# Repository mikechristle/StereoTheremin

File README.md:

# StereoTheremin
II'm sure you are familiar with the Theremin. 
It is a musical instrument that uses hand movements to control pitch and volume. 
One hand controls pitch, and the other hand control volume. 
I like the expressiveness of a no contact instrument,
 but controlling two variables is just too limiting. 
 With my version each hand controls both pitch and volume. 
 The up/down motion controls volume, and the right/left motion controls pitch. 
 This way the right hand plays treble and the left hand plays base, like a piano.
## Code
The micropython code that runs on the Raspberry PI Pico.
## Control
The python code that runs on a PC or a tablet to control the Stereo Theremin.
## PCB
The KiCad files for the printed circuit board. 
Version 10.0.

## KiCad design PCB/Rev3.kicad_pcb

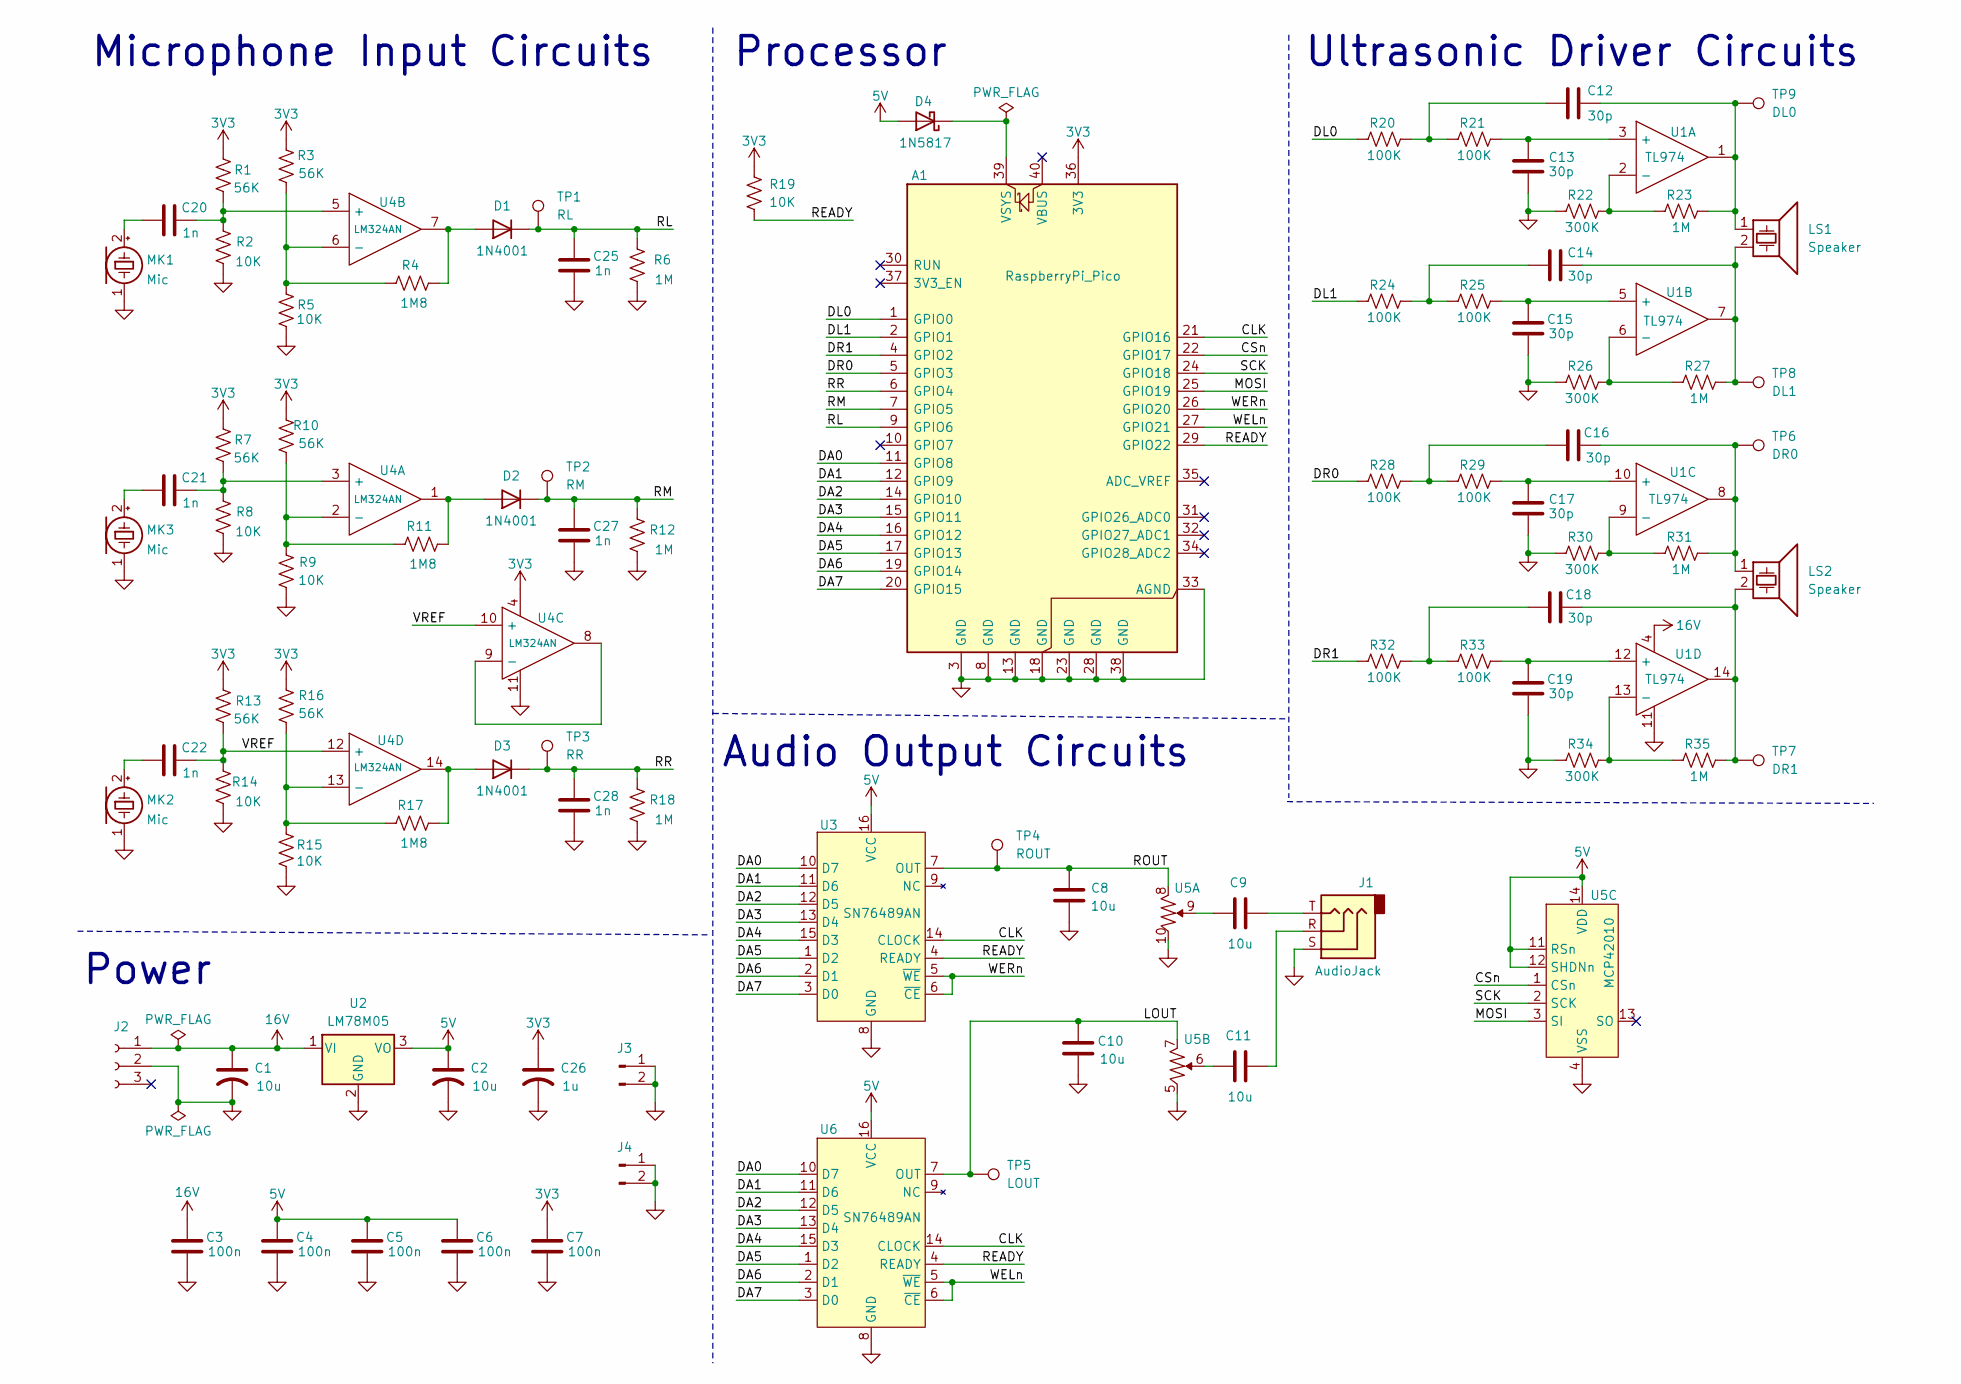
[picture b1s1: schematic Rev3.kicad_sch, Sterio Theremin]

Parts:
A1: RaspberryPi_Pico; RaspberryPi_Pico_Common_THT
C1, C2: 10u; CP_Radial_D6.3mm_P2.50mm
C3, C4, C5, C6, C7: 100n; C_Disc_D3.0mm_W1.6mm_P2.50mm
C8, C9, C10, C11: 10u; C_Disc_D4.3mm_W1.9mm_P5.00mm
C12, C13, C14, C15, C16, C17, C18, C19: 30p; C_Disc_D4.3mm_W1.9mm_P5.00mm
C20, C21, C22, C25, C27, C28: 1n; C_Disc_D4.3mm_W1.9mm_P5.00mm
C26: 1u; CP_Radial_D5.0mm_P2.50mm
D1, D2, D3: 1N4001; D_A-405_P7.62mm_Horizontal
D4: 1N5817; D_A-405_P7.62mm_Horizontal
J1: AudioJack; STX-3000
J2: Conn_01x03_Socket; BarrelJack_Kycon_KLDX-0202-xC_Horizontal
J3, J4: Conn_01x02_Pin; PinHeader_1x02_P2.54mm_Vertical
LS1, LS2: Speaker; Ultra Sonic TR
MK1, MK2, MK3: Mic; Ultra Sonic TR
R1, R3, R7, R10, R13, R16: 56K; R_Axial_DIN0204_L3.6mm_D1.6mm_P5.08mm_Horizontal
R2, R5, R8, R9, R14, R15, R19: 10K; R_Axial_DIN0204_L3.6mm_D1.6mm_P5.08mm_Horizontal
R4, R11, R17: 1M8; R_Axial_DIN0204_L3.6mm_D1.6mm_P5.08mm_Horizontal
R6, R12, R18, R23, R27, R31, R35: 1M; R_Axial_DIN0204_L3.6mm_D1.6mm_P5.08mm_Horizontal
R20, R21, R24, R25, R28, R29, R32, R33: 100K; R_Axial_DIN0204_L3.6mm_D1.6mm_P5.08mm_Horizontal
R22, R26, R30, R34: 300K; R_Axial_DIN0204_L3.6mm_D1.6mm_P5.08mm_Horizontal
TP1: RL; TestPoint_Loop_D2.50mm_Drill1.85mm
TP2: RM; TestPoint_Loop_D2.50mm_Drill1.85mm
TP3: RR; TestPoint_Loop_D2.50mm_Drill1.85mm
TP4: ROUT; TestPoint_Loop_D2.50mm_Drill1.85mm
TP5: LOUT; TestPoint_Loop_D2.50mm_Drill1.85mm
TP6: DR0; TestPoint_Loop_D2.50mm_Drill1.85mm
TP7: DR1; TestPoint_Loop_D2.50mm_Drill1.85mm
TP8: DL1; TestPoint_Loop_D2.50mm_Drill1.85mm
TP9: DL0; TestPoint_Loop_D2.50mm_Drill1.85mm
U1: TL974; DIP-14_W7.62mm
U2: LM78M05; TO-252-2
U3, U6: SN76489AN; DIP-16_W7.62mm
U4: LM324AN; DIP-14_W7.62mm
U5: MCP42010; DIP-14_W7.62mm

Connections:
3V3: A1.36 (3V3), C7.1, C26.1, R1.2, R3.2, R7.2, R10.2, R13.2, R16.2, R19.1, U4.4
5V: C2.1, C4.1, C5.1, C6.1, D4.2 (A), U2.3 (VO), U3.16 (VCC), U5.11 (RSn), U5.12 (SHDNn), U5.14 (VDD), U6.16 (VCC)
16V: C1.1, C3.1, J2.1, U1.4, U2.1 (VI)
/CLK: A1.21 (GPIO16), U3.14 (CLOCK), U6.14 (CLOCK)
/CSn: A1.22 (GPIO17), U5.1 (CSn)
/DA0: A1.11 (GPIO8), U3.10 (D7), U6.10 (D7)
/DA1: A1.12 (GPIO9), U3.11 (D6), U6.11 (D6)
/DA2: A1.14 (GPIO10), U3.12 (D5), U6.12 (D5)
/DA3: A1.15 (GPIO11), U3.13 (D4), U6.13 (D4)
/DA4: A1.16 (GPIO12), U3.15 (D3), U6.15 (D3)
/DA5: A1.17 (GPIO13), U3.1 (D2), U6.1 (D2)
/DA6: A1.19 (GPIO14), U3.2 (D1), U6.2 (D1)
/DA7: A1.20 (GPIO15), U3.3 (D0), U6.3 (D0)
/DL0: A1.1 (GPIO0), R20.1
/DL1: A1.2 (GPIO1), R24.1
/DR0: A1.5 (GPIO3), R28.1
/DR1: A1.4 (GPIO2), R32.1
/LOUT: C10.2, TP5.1 (1_1), U5.7, U6.7 (OUT)
/MOSI: A1.25 (GPIO19), U5.3 (SI)
/READY: A1.29 (GPIO22), R19.2, U3.4 (READY), U6.4 (READY)
/RL: A1.9 (GPIO6), C25.1, D1.1 (K), R6.2, TP1.1 (1_1)
/RM: A1.7 (GPIO5), C27.1, D2.1 (K), R12.2, TP2.1 (1_1)
/ROUT: C8.2, TP4.1 (1_1), U3.7 (OUT), U5.8
/RR: A1.6 (GPIO4), C28.1, D3.1 (K), R18.2, TP3.1 (1_1)
/SCK: A1.24 (GPIO18), U5.2 (SCK)
/VREF: C22.2, R13.1, R14.2, U4.10 (+), U4.12 (+)
/WELn: A1.27 (GPIO21), U6.5 (~WE), U6.6 (~CE)
/WERn: A1.26 (GPIO20), U3.5 (~WE), U3.6 (~CE)
GND: A1.3 (GND), A1.8 (GND), A1.13 (GND), A1.18 (GND), A1.23 (GND), A1.28 (GND), A1.33 (AGND), A1.38 (GND), C1.2, C2.2, C3.2, C4.2, C5.2, C6.2, C7.2, C8.1, C10.1, C13.2, C15.2, C17.2, C19.2, C25.2, C26.2, C27.2, C28.2, J1.S, J2.2, J3.1, J3.2, J4.1, J4.2, MK1.1 (-), MK2.1 (-), MK3.1 (-), R2.1, R5.2, R6.1, R8.1, R9.2, R12.1, R14.1, R15.2, R18.1, R22.1, R26.1, R30.1, R34.1, U1.11, U2.2 (GND), U3.8 (GND), U4.11, U5.4 (VSS), U5.5, U5.10, U6.8 (GND)
unnamed: A1.39 (VSYS), D4.1 (K)
unnamed: C9.1, J1.T
unnamed: C9.2, U5.9
unnamed: C11.1, J1.R
unnamed: C11.2, U5.6
unnamed: C12.1, R20.2, R21.1
unnamed: C12.2, LS1.1, R23.2, TP9.1 (1_1), U1.1
unnamed: C14.1, R24.2, R25.1
unnamed: C14.2, LS1.2, R27.2, TP8.1 (1_1), U1.7
unnamed: C16.1, R28.2, R29.1
unnamed: C16.2, LS2.1, R31.2, TP6.1 (1_1), U1.8
unnamed: C18.1, R32.2, R33.1
unnamed: C18.2, LS2.2, R35.2, TP7.1 (1_1), U1.14
unnamed: D1.2 (A), R4.2, U4.7
unnamed: D2.2 (A), R11.2, U4.1
unnamed: D3.2 (A), R17.2, U4.14
unnamed: C20.1, MK1.2 (+)
unnamed: C22.1, MK2.2 (+)
unnamed: C21.1, MK3.2 (+)
unnamed: C13.1, R21.2, U1.3 (+)
unnamed: R22.2, R23.1, U1.2 (-)
unnamed: C15.1, R25.2, U1.5 (+)
unnamed: R26.2, R27.1, U1.6 (-)
unnamed: C17.1, R29.2, U1.10 (+)
unnamed: R30.2, R31.1, U1.9 (-)
unnamed: C19.1, R33.2, U1.12 (+)
unnamed: R34.2, R35.1, U1.13 (-)
unnamed: C21.2, R7.1, R8.2, U4.3 (+)
unnamed: R9.1, R10.1, R11.1, U4.2 (-)
unnamed: C20.2, R1.1, R2.2, U4.5 (+)
unnamed: R3.1, R4.1, R5.1, U4.6 (-)
unnamed: U4.8, U4.9 (-)
unnamed: R15.1, R16.1, R17.1, U4.13 (-)

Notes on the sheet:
Audio Output Circuits
Processor
Power
Microphone Input Circuits
Ultrasonic Driver Circuits

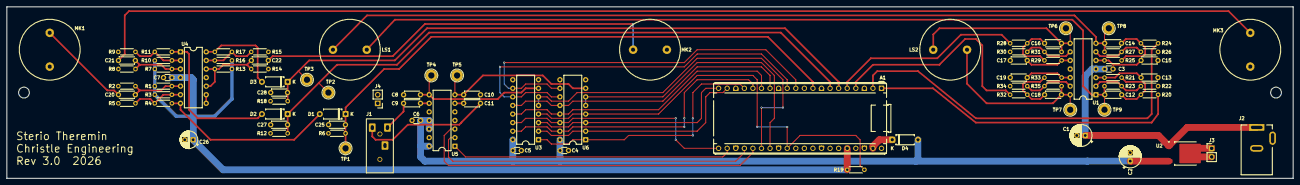
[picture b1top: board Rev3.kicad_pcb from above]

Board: 2 copper layers, 381.0 x 50.8 mm, 90 parts (0 on the bottom side), 62 nets.

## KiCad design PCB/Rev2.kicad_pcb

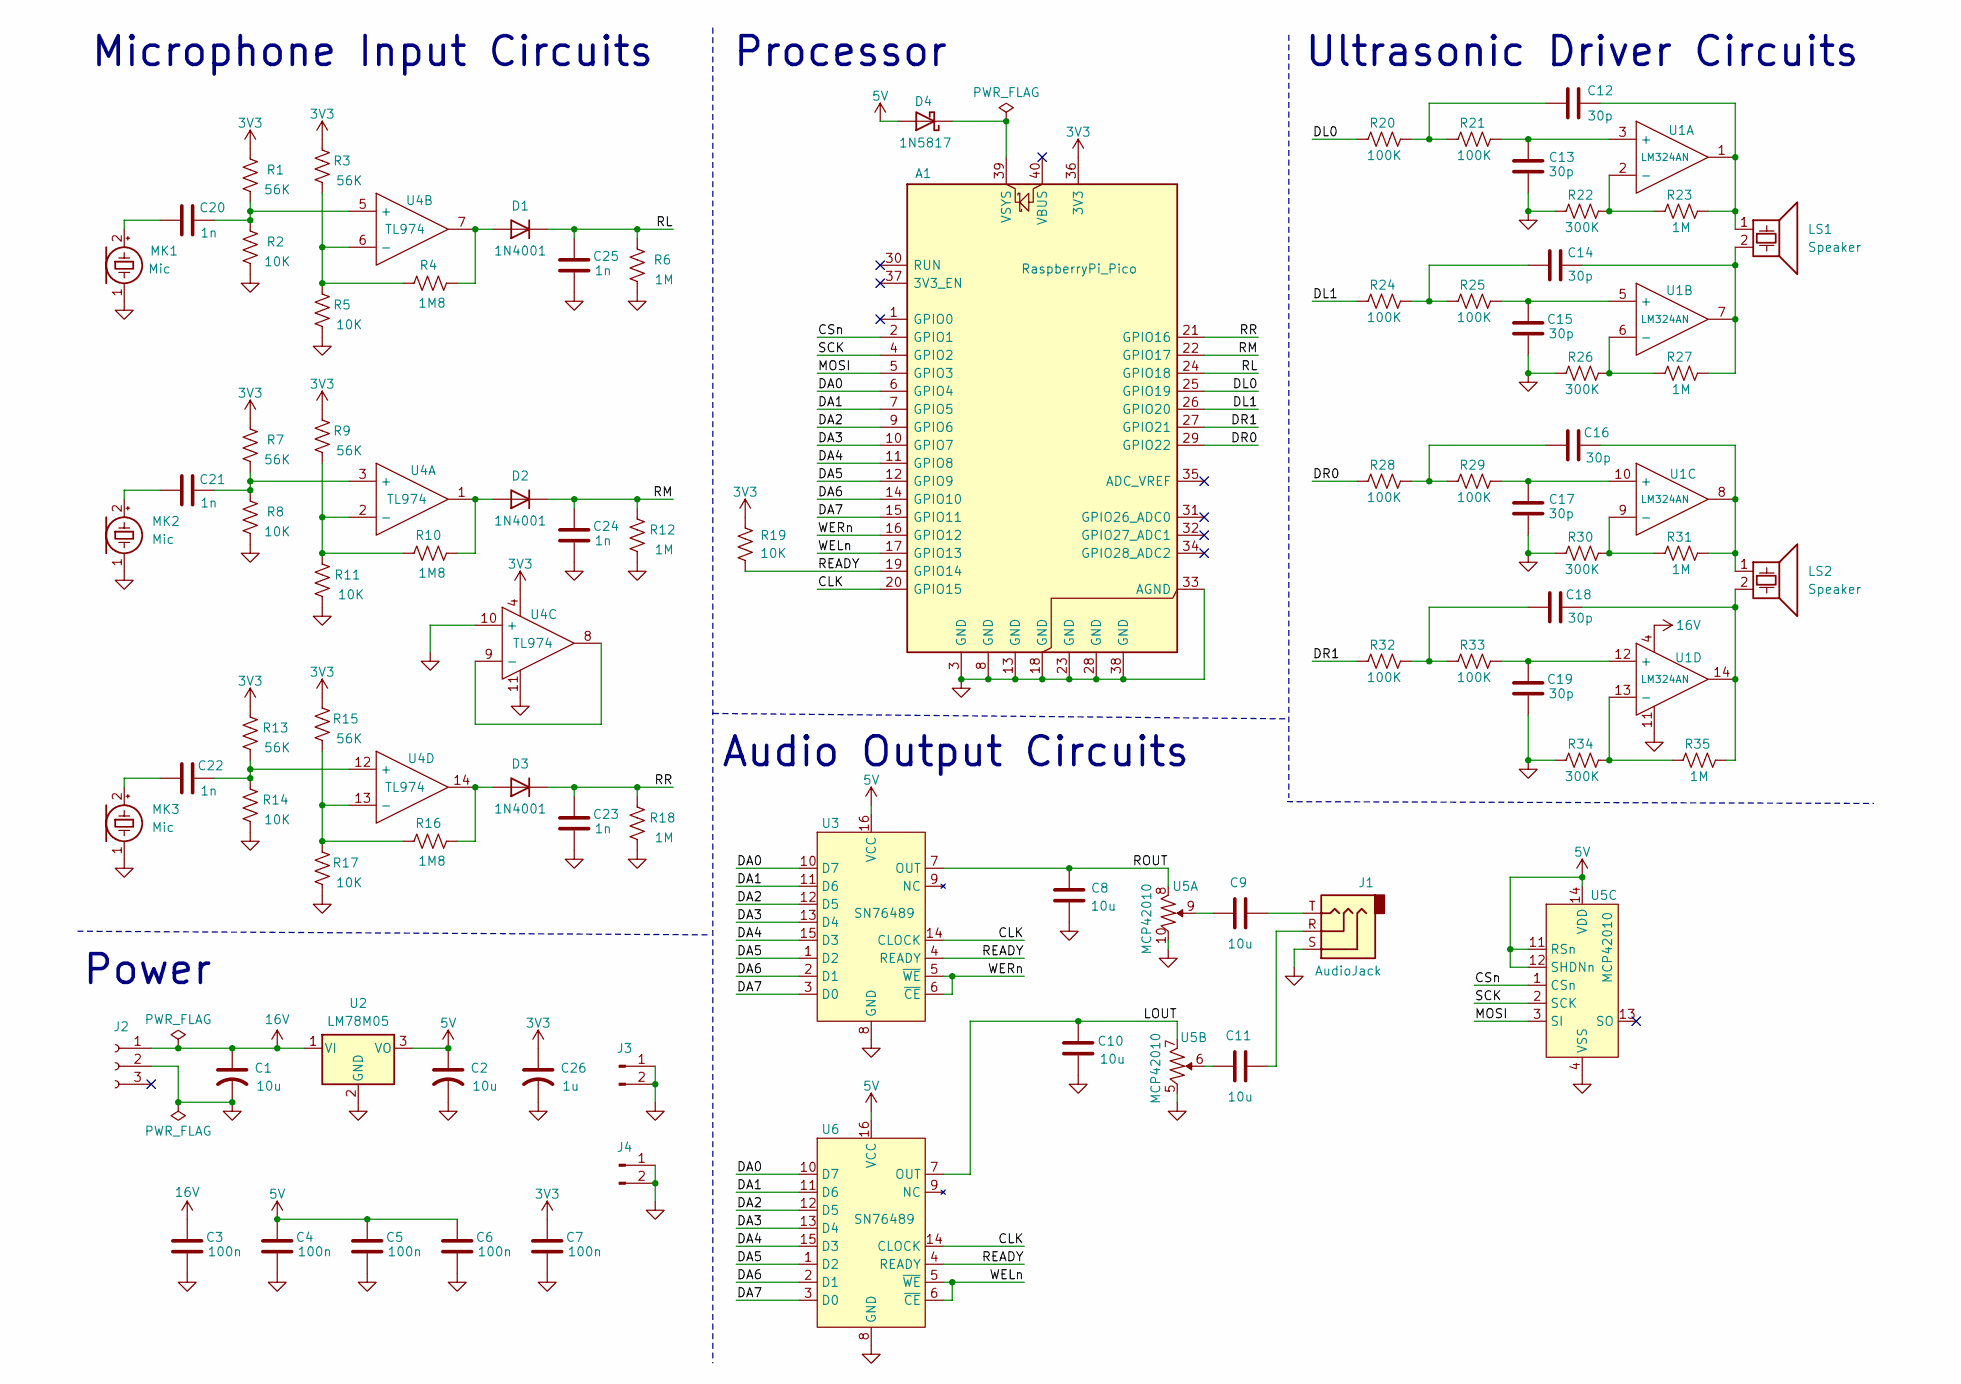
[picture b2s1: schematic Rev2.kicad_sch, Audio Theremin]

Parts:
A1: RaspberryPi_Pico; RaspberryPi_Pico_Common_THT
C1, C2: 10u; CP_Radial_D6.3mm_P2.50mm
C3, C4, C5, C6, C7: 100n; C_Disc_D3.0mm_W1.6mm_P2.50mm
C8, C9, C10, C11: 10u; C_Disc_D4.3mm_W1.9mm_P5.00mm
C12, C13, C14, C15, C16, C17, C18, C19: 30p; C_Disc_D4.3mm_W1.9mm_P5.00mm
C20, C21, C22, C23, C24, C25: 1n; C_Disc_D4.3mm_W1.9mm_P5.00mm
C26: 1u; CP_Radial_D5.0mm_P2.50mm
D1, D2, D3: 1N4001; D_DO-41_SOD81_P10.16mm_Horizontal
D4: 1N5817; D_DO-41_SOD81_P10.16mm_Horizontal
J1: AudioJack; STX-3000
J2: Conn_01x03_Socket; BarrelJack_Kycon_KLDX-0202-xC_Horizontal
J3, J4: Conn_01x02_Pin; PinHeader_1x02_P2.54mm_Vertical
LS1, LS2: Speaker; PinHeader_1x02_P2.54mm_Vertical
MK1, MK2, MK3: Mic; PinHeader_1x02_P2.54mm_Vertical
R1, R3, R7, R9, R13, R15: 56K; R_Axial_DIN0204_L3.6mm_D1.6mm_P5.08mm_Horizontal
R2, R5, R8, R11, R14, R17, R19: 10K; R_Axial_DIN0204_L3.6mm_D1.6mm_P5.08mm_Horizontal
R4, R10, R16: 1M8; R_Axial_DIN0204_L3.6mm_D1.6mm_P5.08mm_Horizontal
R6, R12, R18, R23, R27, R31, R35: 1M; R_Axial_DIN0204_L3.6mm_D1.6mm_P5.08mm_Horizontal
R20, R21, R24, R25, R28, R29, R32, R33: 100K; R_Axial_DIN0204_L3.6mm_D1.6mm_P5.08mm_Horizontal
R22, R26, R30, R34: 300K; R_Axial_DIN0204_L3.6mm_D1.6mm_P5.08mm_Horizontal
U1: LM324AN; DIP-14_W7.62mm
U2: LM78M05; TO-252-2
U3, U6: SN76489; DIP-16_W7.62mm
U4: TL974; DIP-14_W7.62mm
U5: MCP42010; DIP-14_W7.62mm

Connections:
3V3: A1.36 (3V3), C7.1, C26.1, R1.2, R3.2, R7.2, R9.2, R13.2, R15.2, R19.1, U4.4
5V: C2.1, C4.1, C5.1, C6.1, D4.2 (A), U2.3 (VO), U3.16 (VCC), U5.11 (RSn), U5.12 (SHDNn), U5.14 (VDD), U6.16 (VCC)
16V: C1.1, C3.1, J2.1, U1.4, U2.1 (VI)
/CLK: A1.20 (GPIO15), U3.14 (CLOCK), U6.14 (CLOCK)
/CSn: A1.2 (GPIO1), U5.1 (CSn)
/DA0: A1.6 (GPIO4), U3.10 (D7), U6.10 (D7)
/DA1: A1.7 (GPIO5), U3.11 (D6), U6.11 (D6)
/DA2: A1.9 (GPIO6), U3.12 (D5), U6.12 (D5)
/DA3: A1.10 (GPIO7), U3.13 (D4), U6.13 (D4)
/DA4: A1.11 (GPIO8), U3.15 (D3), U6.15 (D3)
/DA5: A1.12 (GPIO9), U3.1 (D2), U6.1 (D2)
/DA6: A1.14 (GPIO10), U3.2 (D1), U6.2 (D1)
/DA7: A1.15 (GPIO11), U3.3 (D0), U6.3 (D0)
/DL0: A1.25 (GPIO19), R20.1
/DL1: A1.26 (GPIO20), R24.1
/DR0: A1.29 (GPIO22), R28.1
/DR1: A1.27 (GPIO21), R32.1
/LOUT: C10.2, U5.7, U6.7 (OUT)
/MOSI: A1.5 (GPIO3), U5.3 (SI)
/READY: A1.19 (GPIO14), R19.2, U3.4 (READY), U6.4 (READY)
/RL: A1.24 (GPIO18), C25.1, D1.1 (K), R6.2
/RM: A1.22 (GPIO17), C24.1, D2.1 (K), R12.2
/ROUT: C8.2, U3.7 (OUT), U5.8
/RR: A1.21 (GPIO16), C23.1, D3.1 (K), R18.2
/SCK: A1.4 (GPIO2), U5.2 (SCK)
/WELn: A1.17 (GPIO13), U6.5 (~WE), U6.6 (~CE)
/WERn: A1.16 (GPIO12), U3.5 (~WE), U3.6 (~CE)
GND: A1.3 (GND), A1.8 (GND), A1.13 (GND), A1.18 (GND), A1.23 (GND), A1.28 (GND), A1.33 (AGND), A1.38 (GND), C1.2, C2.2, C3.2, C4.2, C5.2, C6.2, C7.2, C8.1, C10.1, C13.2, C15.2, C17.2, C19.2, C23.2, C24.2, C25.2, C26.2, J1.S, J2.2, J3.1, J3.2, J4.1, J4.2, MK1.1 (-), MK2.1 (-), MK3.1 (-), R2.1, R5.1, R6.1, R8.1, R11.1, R12.1, R14.1, R17.1, R18.1, R22.1, R26.1, R30.1, R34.1, U1.11, U2.2 (GND), U3.8 (GND), U4.10 (+), U4.11, U5.4 (VSS), U5.5, U5.10, U6.8 (GND)
unnamed: A1.39 (VSYS), D4.1 (K)
unnamed: C9.1, J1.T
unnamed: C9.2, U5.9
unnamed: C11.1, J1.R
unnamed: C11.2, U5.6
unnamed: C12.1, R20.2, R21.1
unnamed: C12.2, LS1.1, R23.2, U1.1
unnamed: C14.1, R24.2, R25.1
unnamed: C14.2, LS1.2, R27.2, U1.7
unnamed: C16.1, R28.2, R29.1
unnamed: C16.2, LS2.1, R31.2, U1.8
unnamed: C18.1, R32.2, R33.1
unnamed: C18.2, LS2.2, R35.2, U1.14
unnamed: D1.2 (A), R4.2, U4.7
unnamed: D2.2 (A), R10.2, U4.1
unnamed: D3.2 (A), R16.2, U4.14
unnamed: C20.1, MK1.2 (+)
unnamed: C21.1, MK2.2 (+)
unnamed: C22.1, MK3.2 (+)
unnamed: C13.1, R21.2, U1.3 (+)
unnamed: R22.2, R23.1, U1.2 (-)
unnamed: C15.1, R25.2, U1.5 (+)
unnamed: R26.2, R27.1, U1.6 (-)
unnamed: C17.1, R29.2, U1.10 (+)
unnamed: R30.2, R31.1, U1.9 (-)
unnamed: C19.1, R33.2, U1.12 (+)
unnamed: R34.2, R35.1, U1.13 (-)
unnamed: C21.2, R7.1, R8.2, U4.3 (+)
unnamed: R9.1, R10.1, R11.2, U4.2 (-)
unnamed: C20.2, R1.1, R2.2, U4.5 (+)
unnamed: R3.1, R4.1, R5.2, U4.6 (-)
unnamed: U4.8, U4.9 (-)
unnamed: C22.2, R13.1, R14.2, U4.12 (+)
unnamed: R15.1, R16.1, R17.2, U4.13 (-)

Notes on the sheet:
Audio Output Circuits
Processor
Power
Microphone Input Circuits
Ultrasonic Driver Circuits

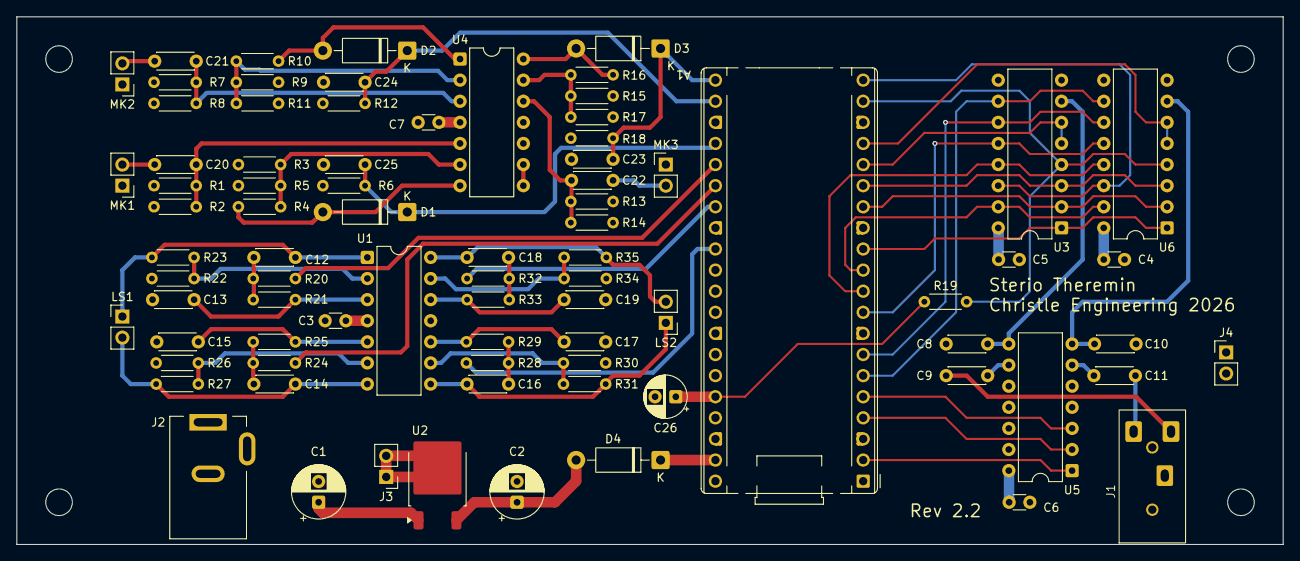
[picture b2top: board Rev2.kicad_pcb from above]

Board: 4 copper layers, 152.4 x 63.5 mm, 85 parts (0 on the bottom side), 62 nets.

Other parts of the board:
MH1, MH2, MH3, MH4: MountingHole_3.2mm_M3

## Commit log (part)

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2026-05-24 Update README.md
    Expanded text.
2026-05-25 Update README.md
    Correct spelling.
2026-05-27 Initial release
2026-05-27 Add subfolder descriptions.
2026-06-01 Create main.py
    Initial release.
2026-06-01 Add files via upload
    Initial release.
2026-06-09 Doubled gain on receiver circuits.
2026-06-22 Add files via upload
    Changed default output voltage on receiver circuit. Added ground points, J4.
